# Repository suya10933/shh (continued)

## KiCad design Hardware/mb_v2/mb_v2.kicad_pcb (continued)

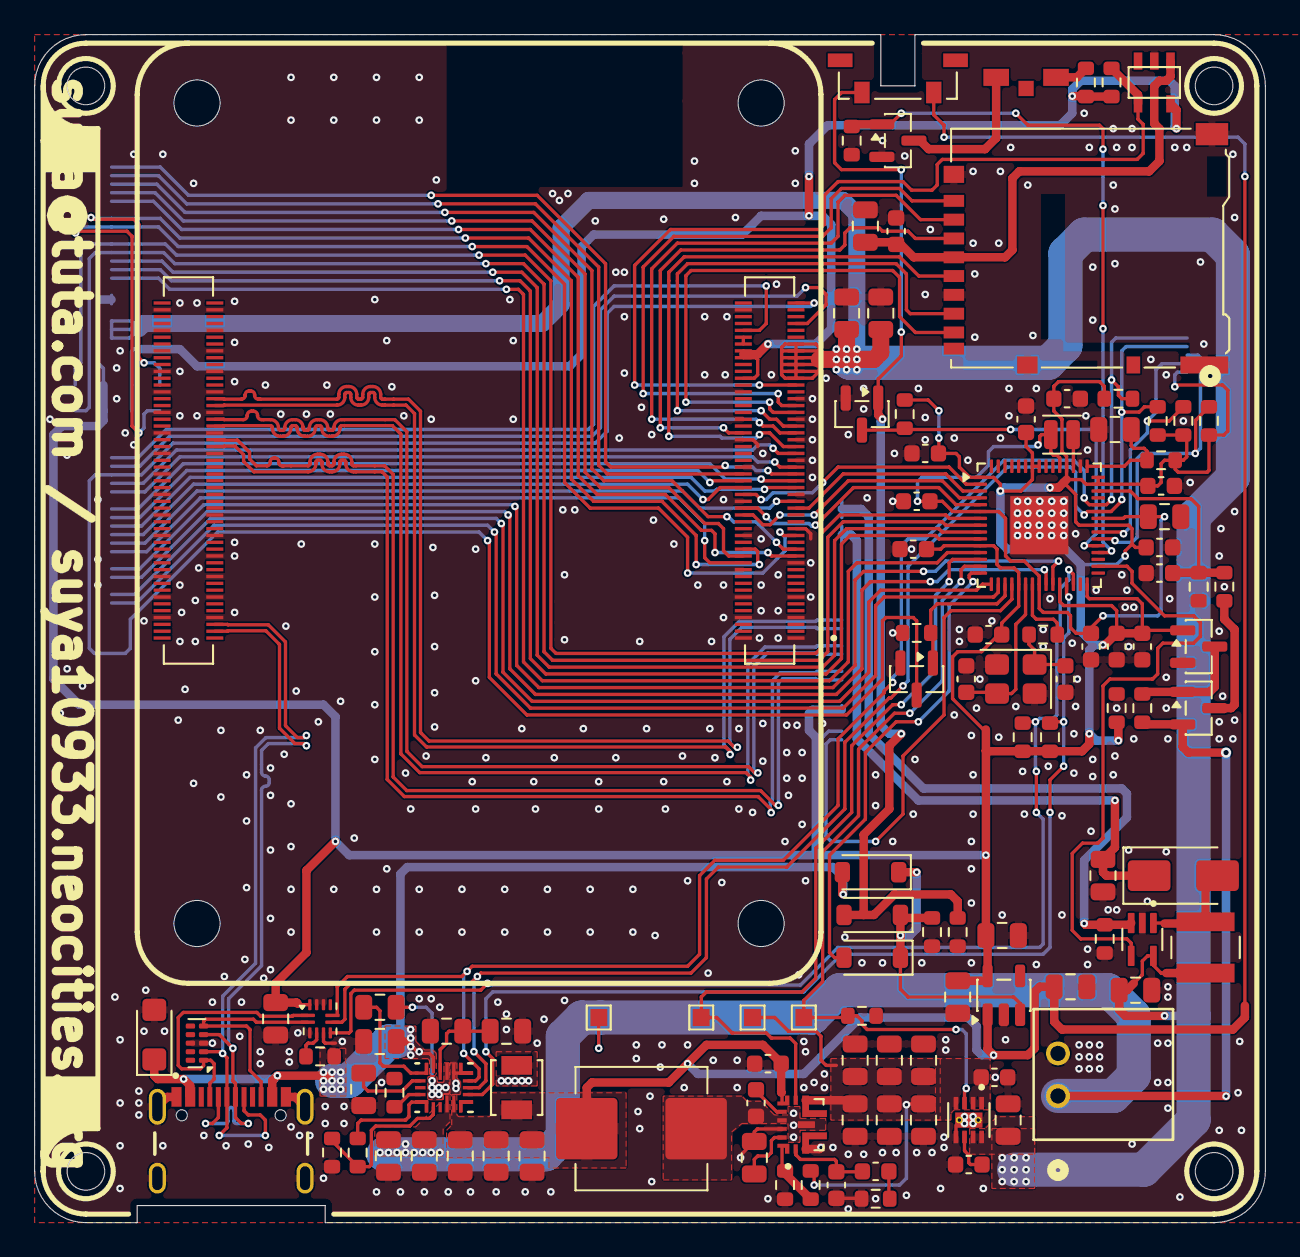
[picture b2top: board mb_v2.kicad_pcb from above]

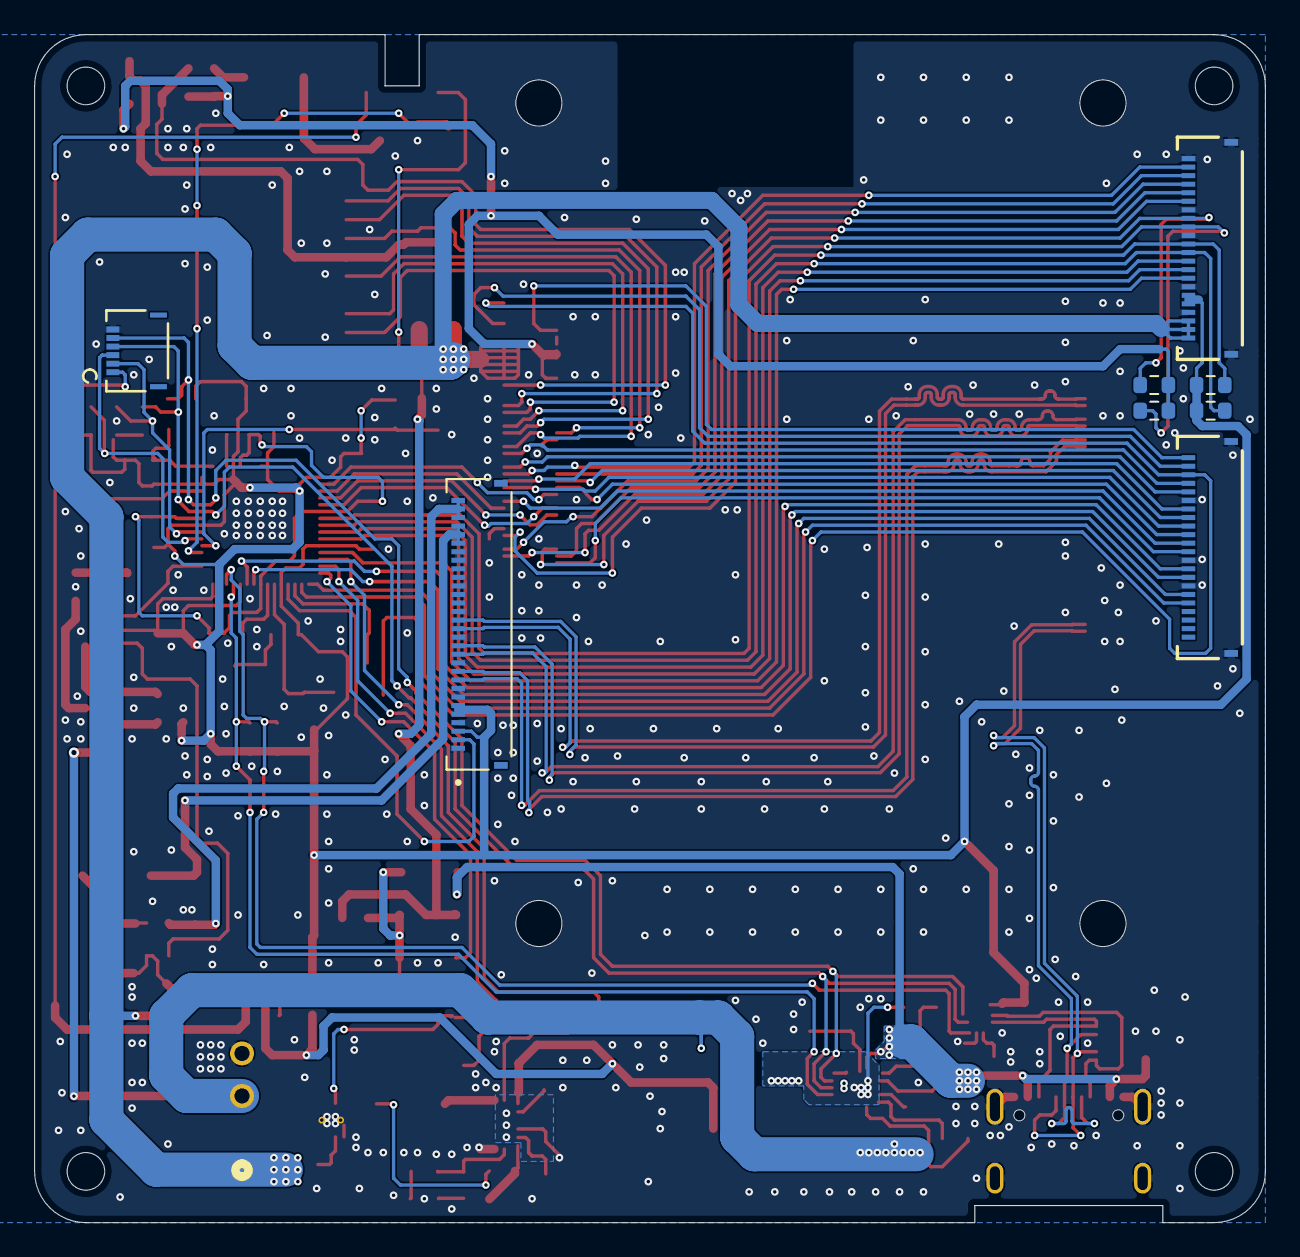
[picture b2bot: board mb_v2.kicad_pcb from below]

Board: 4 copper layers, 72.0 x 69.5 mm, 120 parts (8 on the bottom side), 103 nets.

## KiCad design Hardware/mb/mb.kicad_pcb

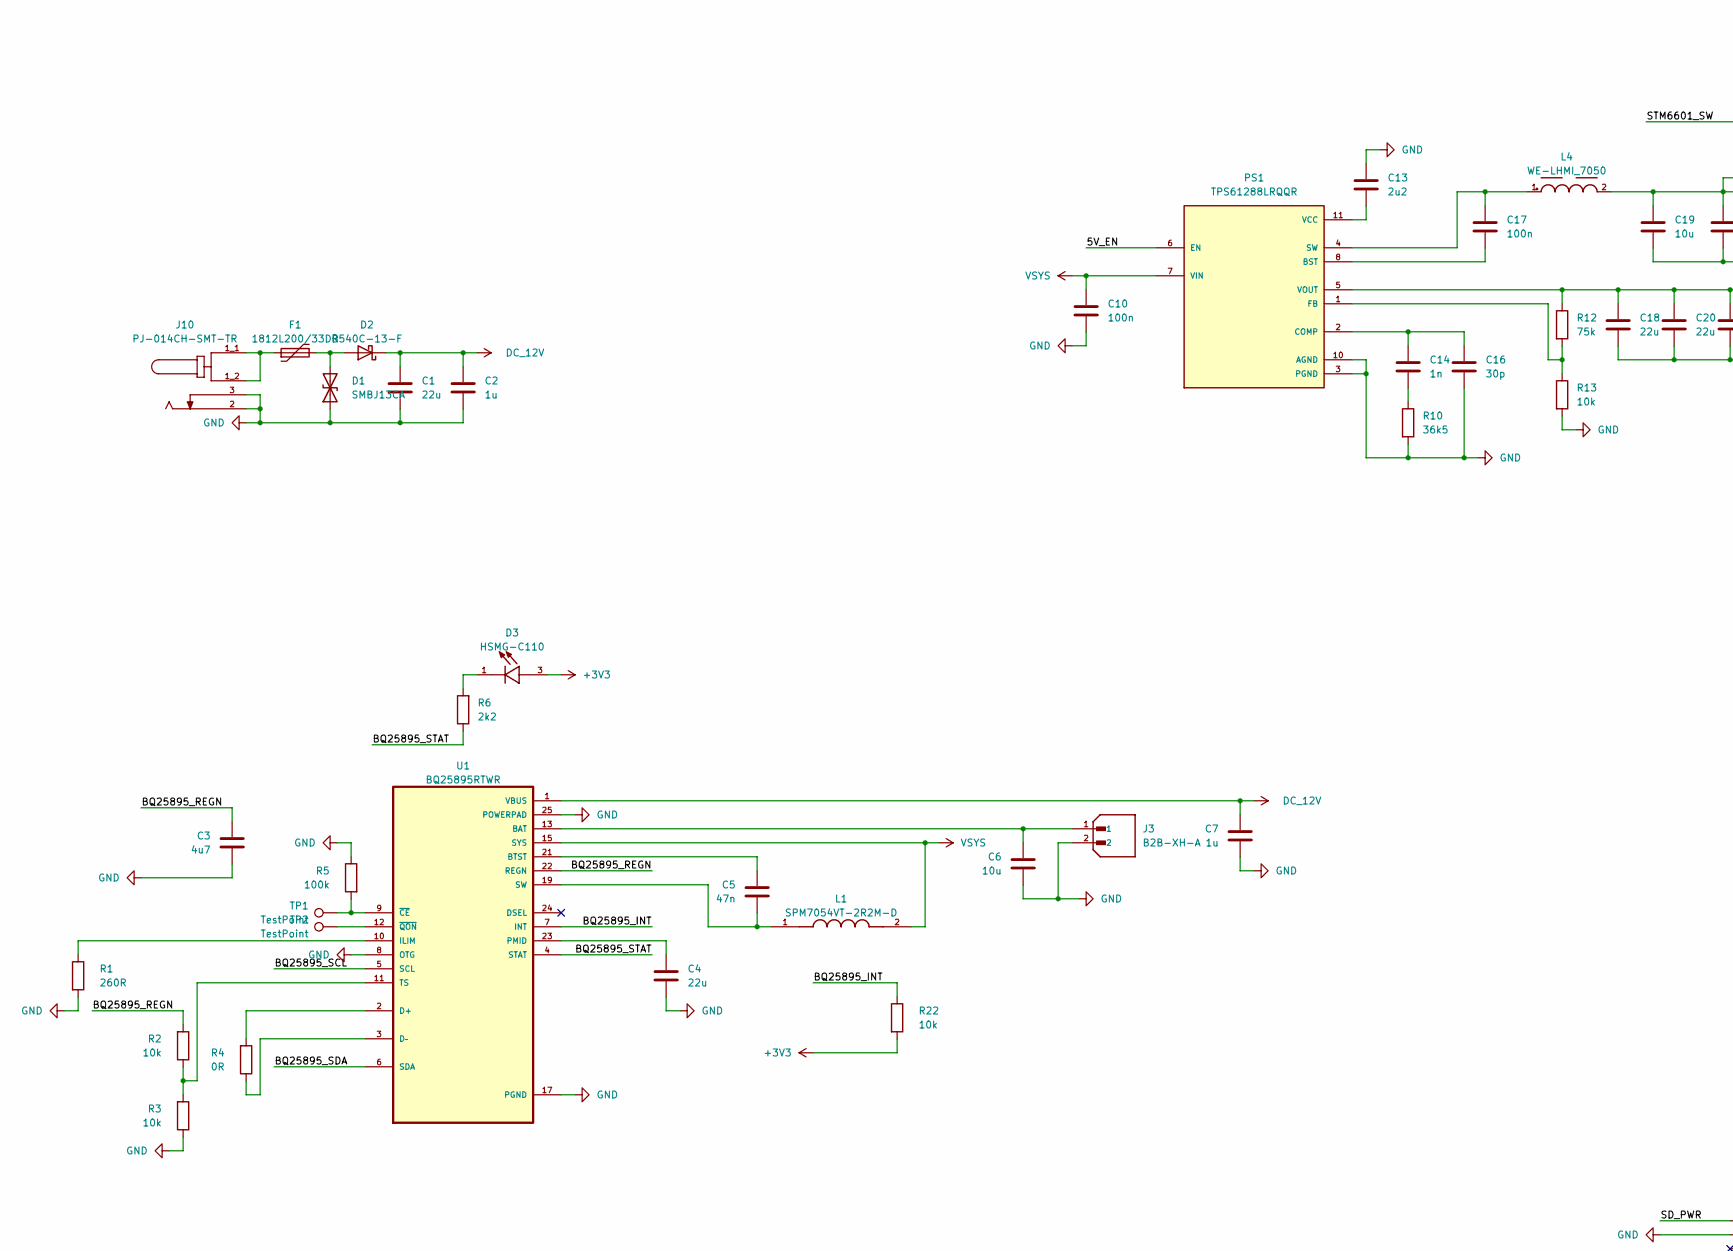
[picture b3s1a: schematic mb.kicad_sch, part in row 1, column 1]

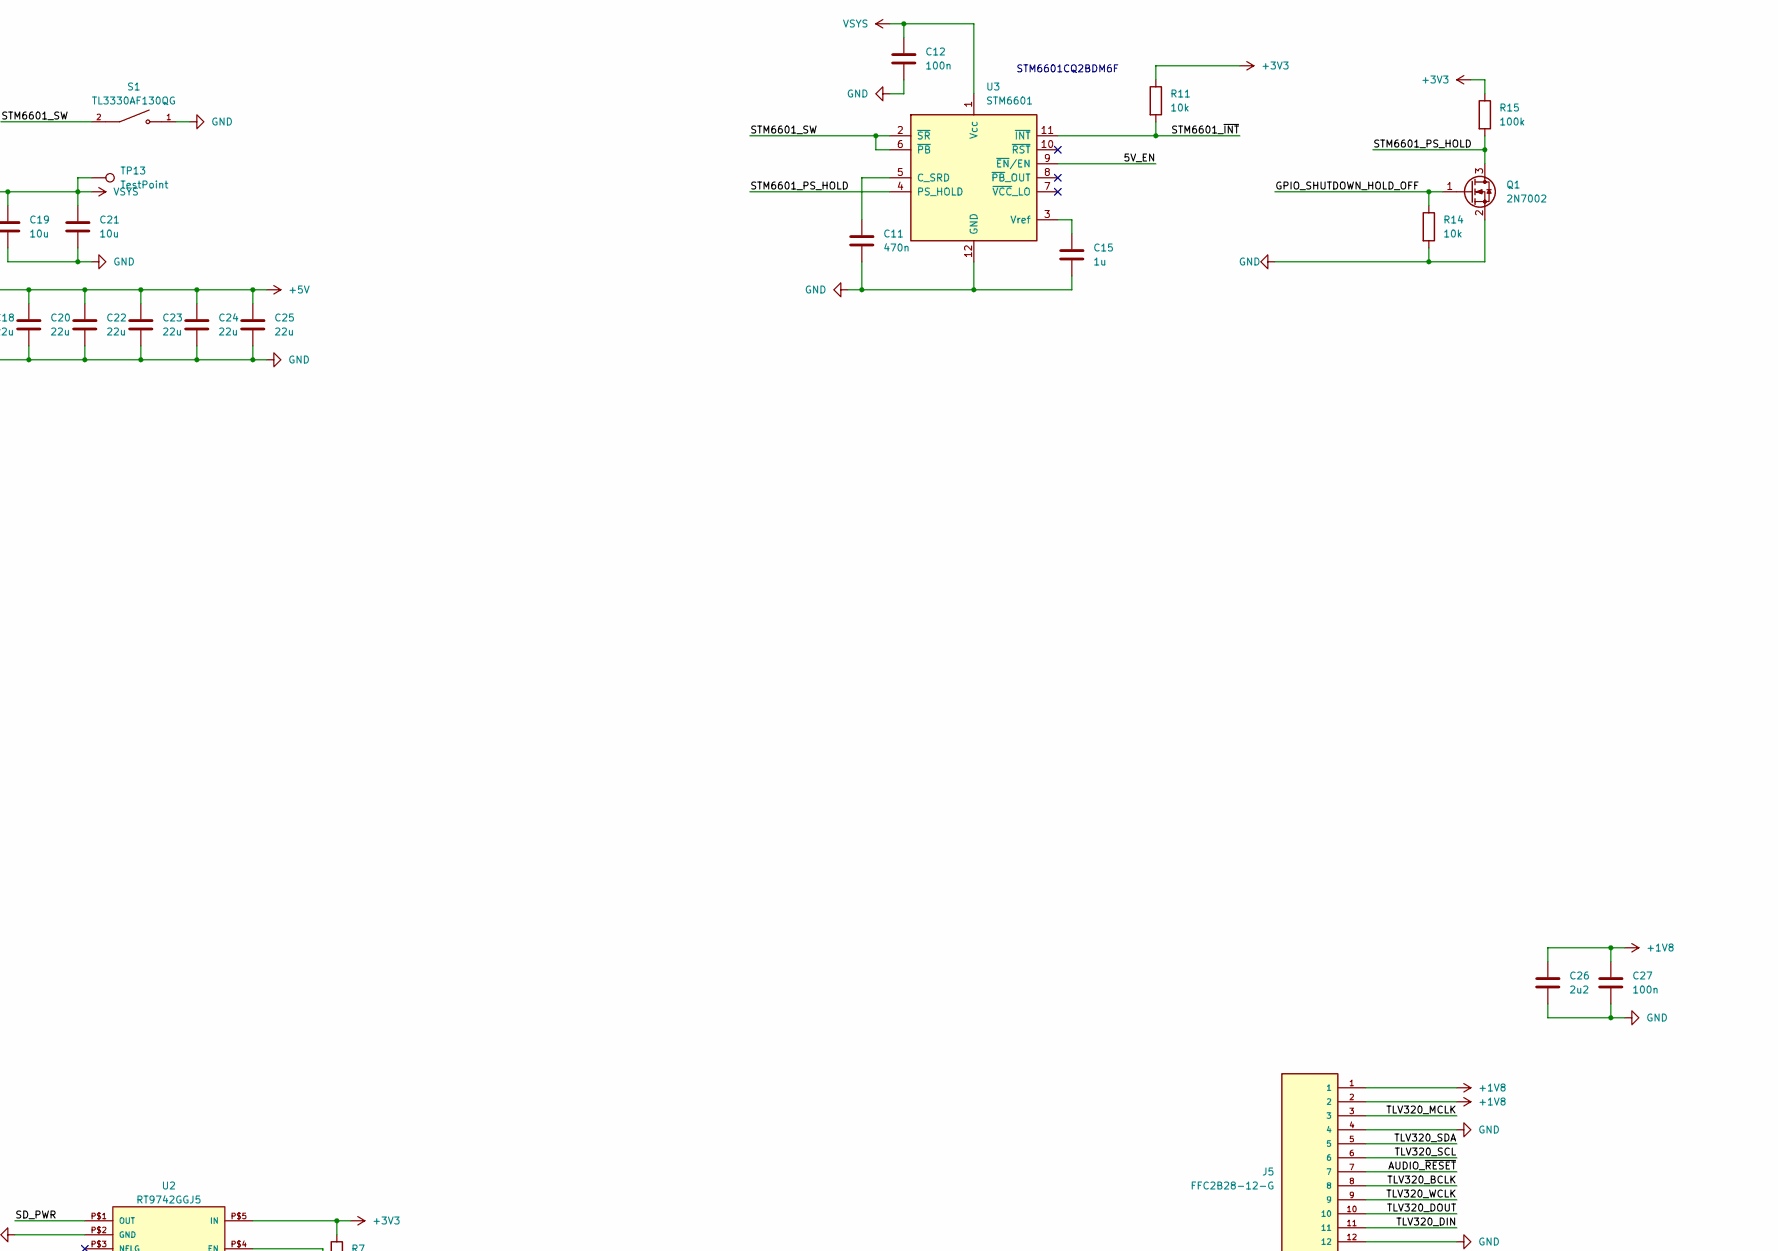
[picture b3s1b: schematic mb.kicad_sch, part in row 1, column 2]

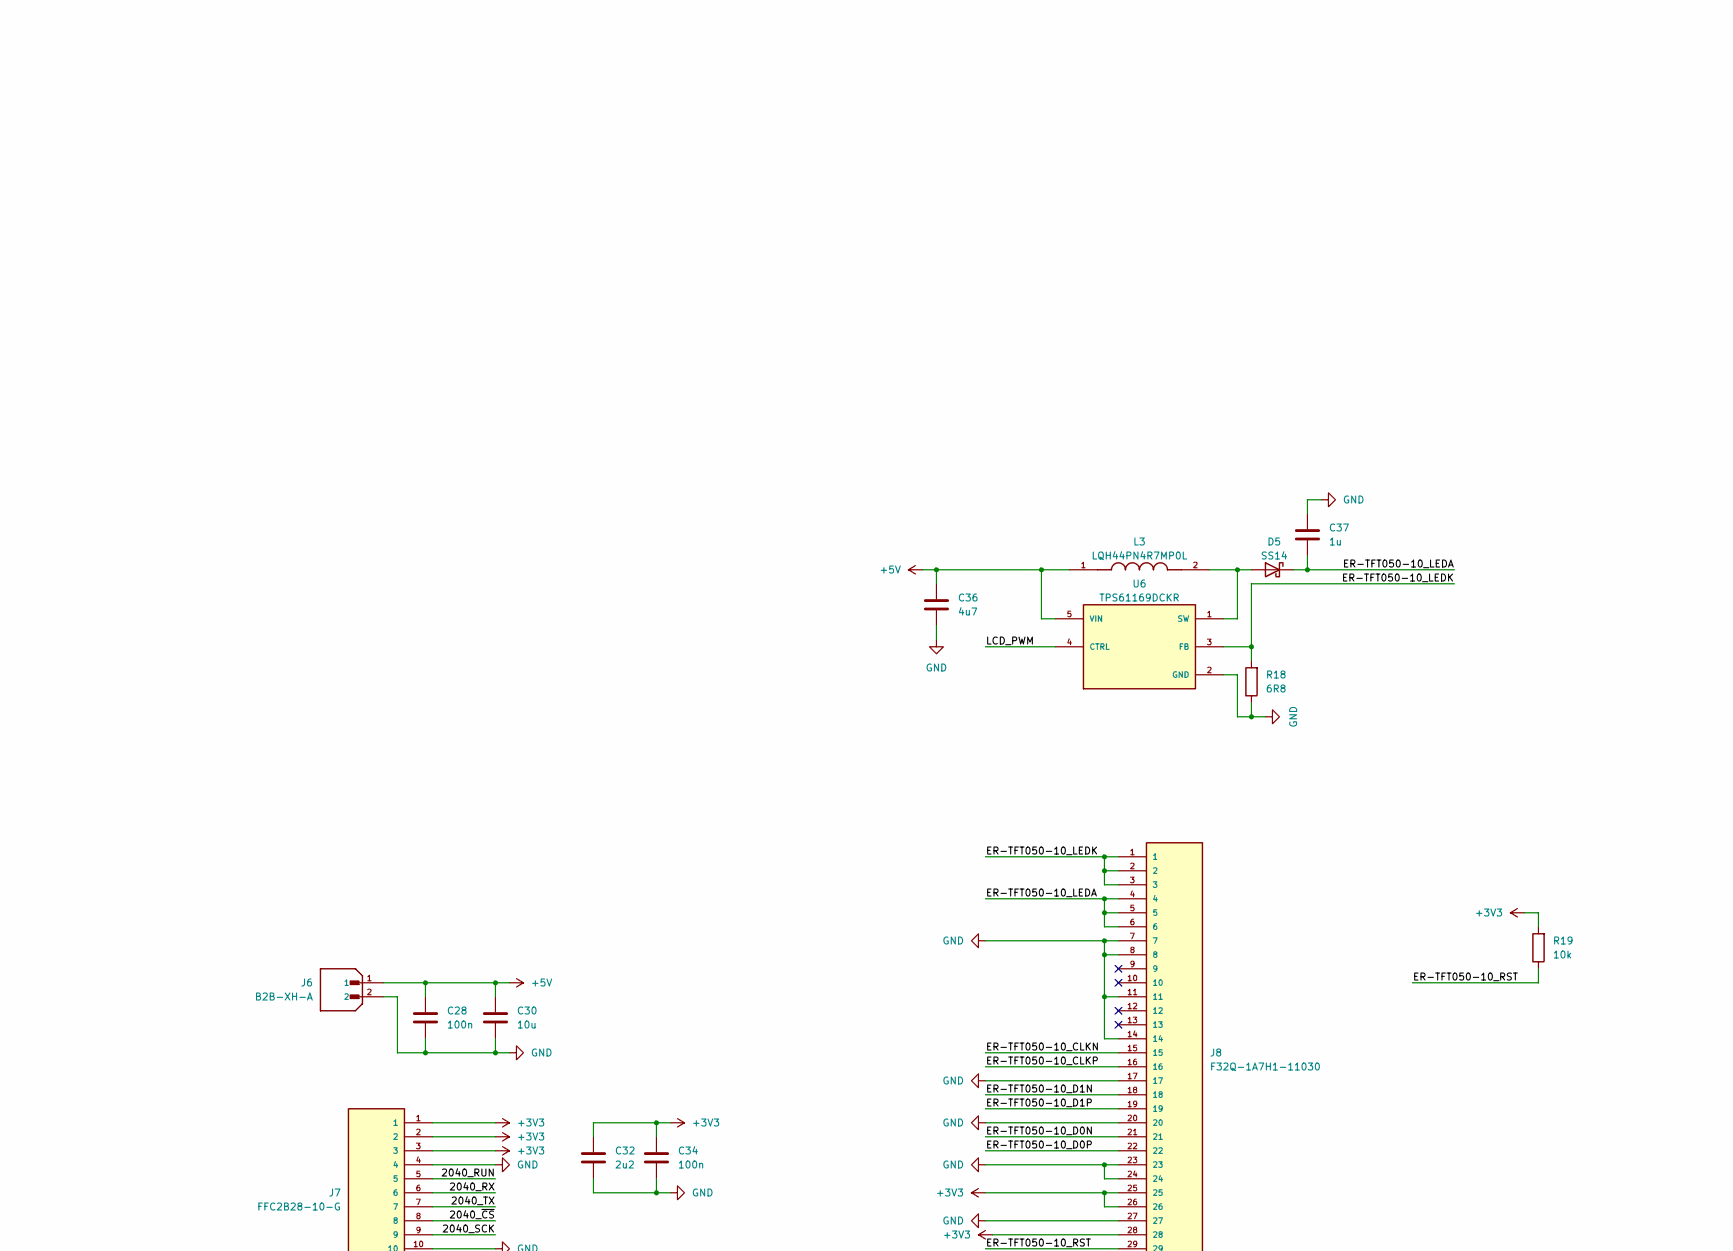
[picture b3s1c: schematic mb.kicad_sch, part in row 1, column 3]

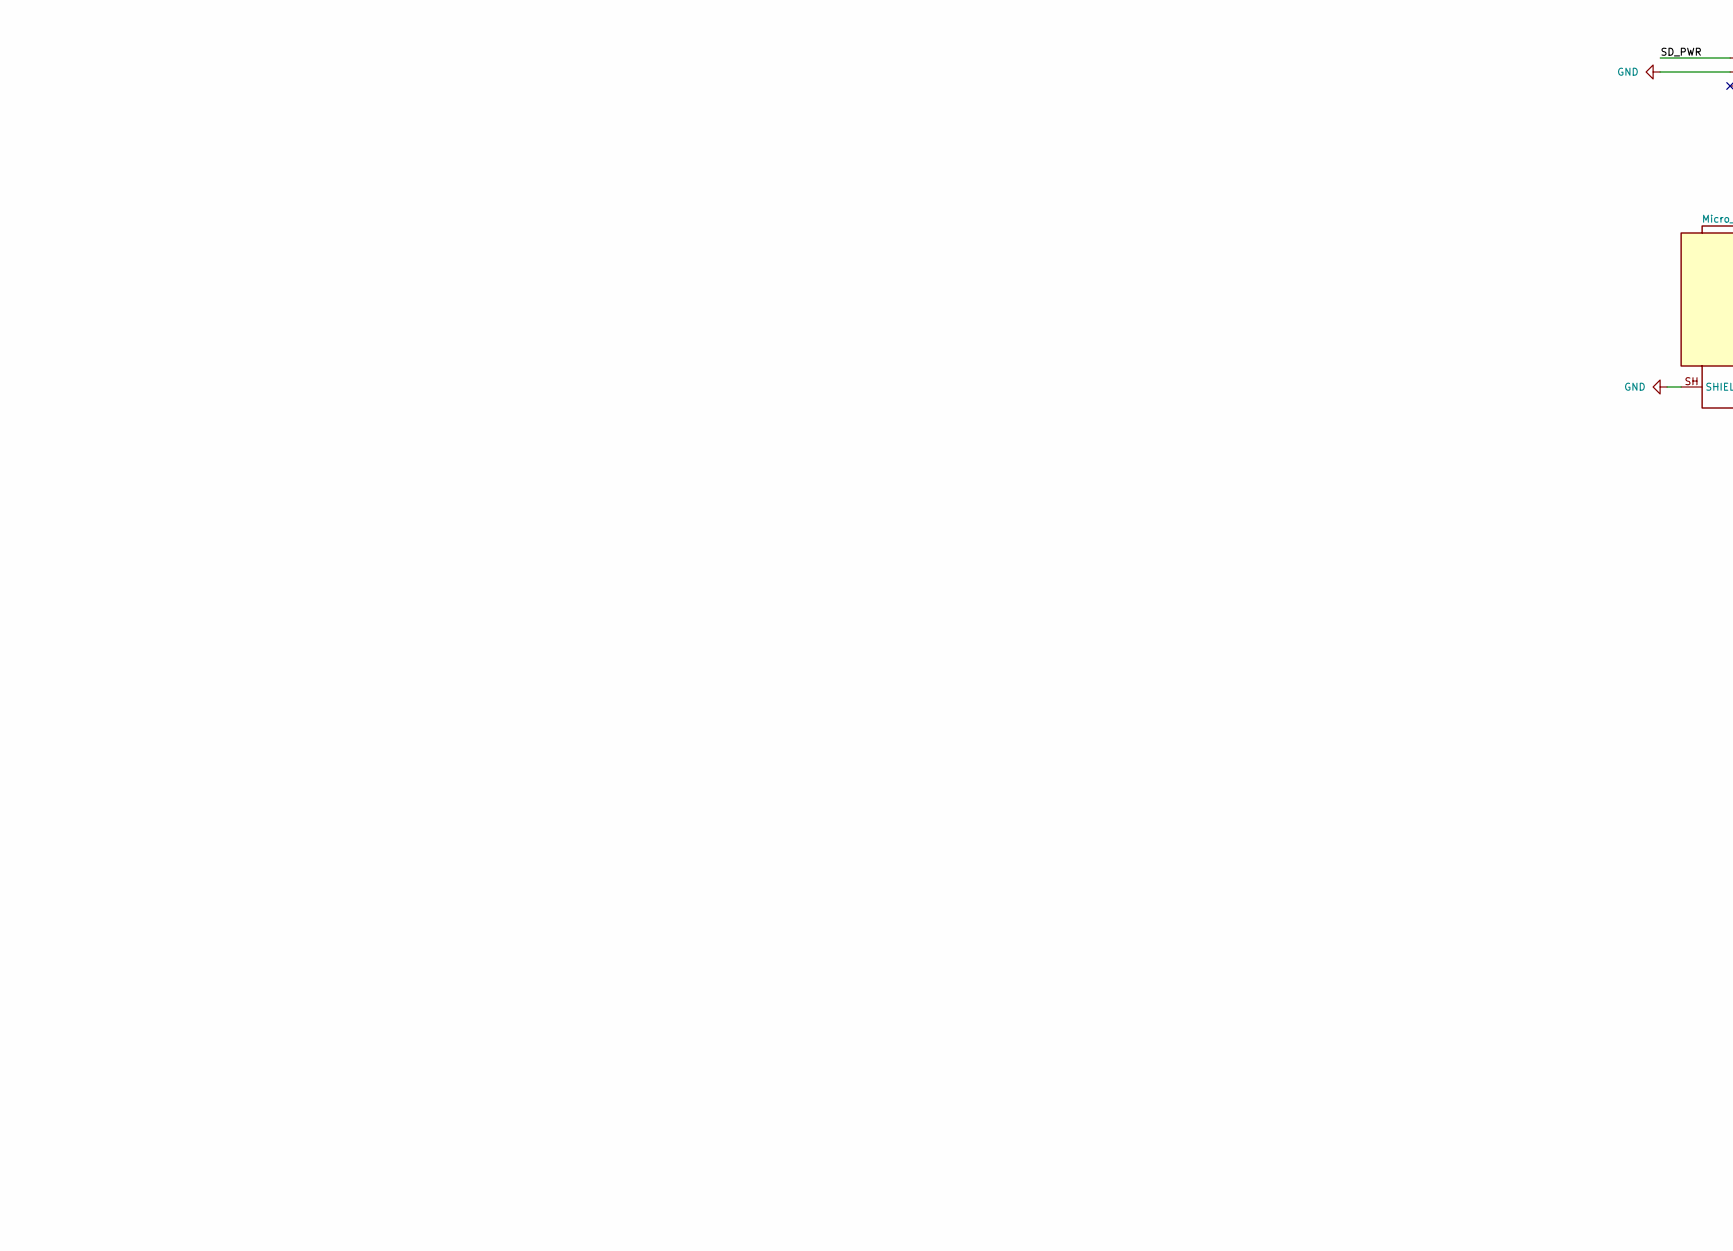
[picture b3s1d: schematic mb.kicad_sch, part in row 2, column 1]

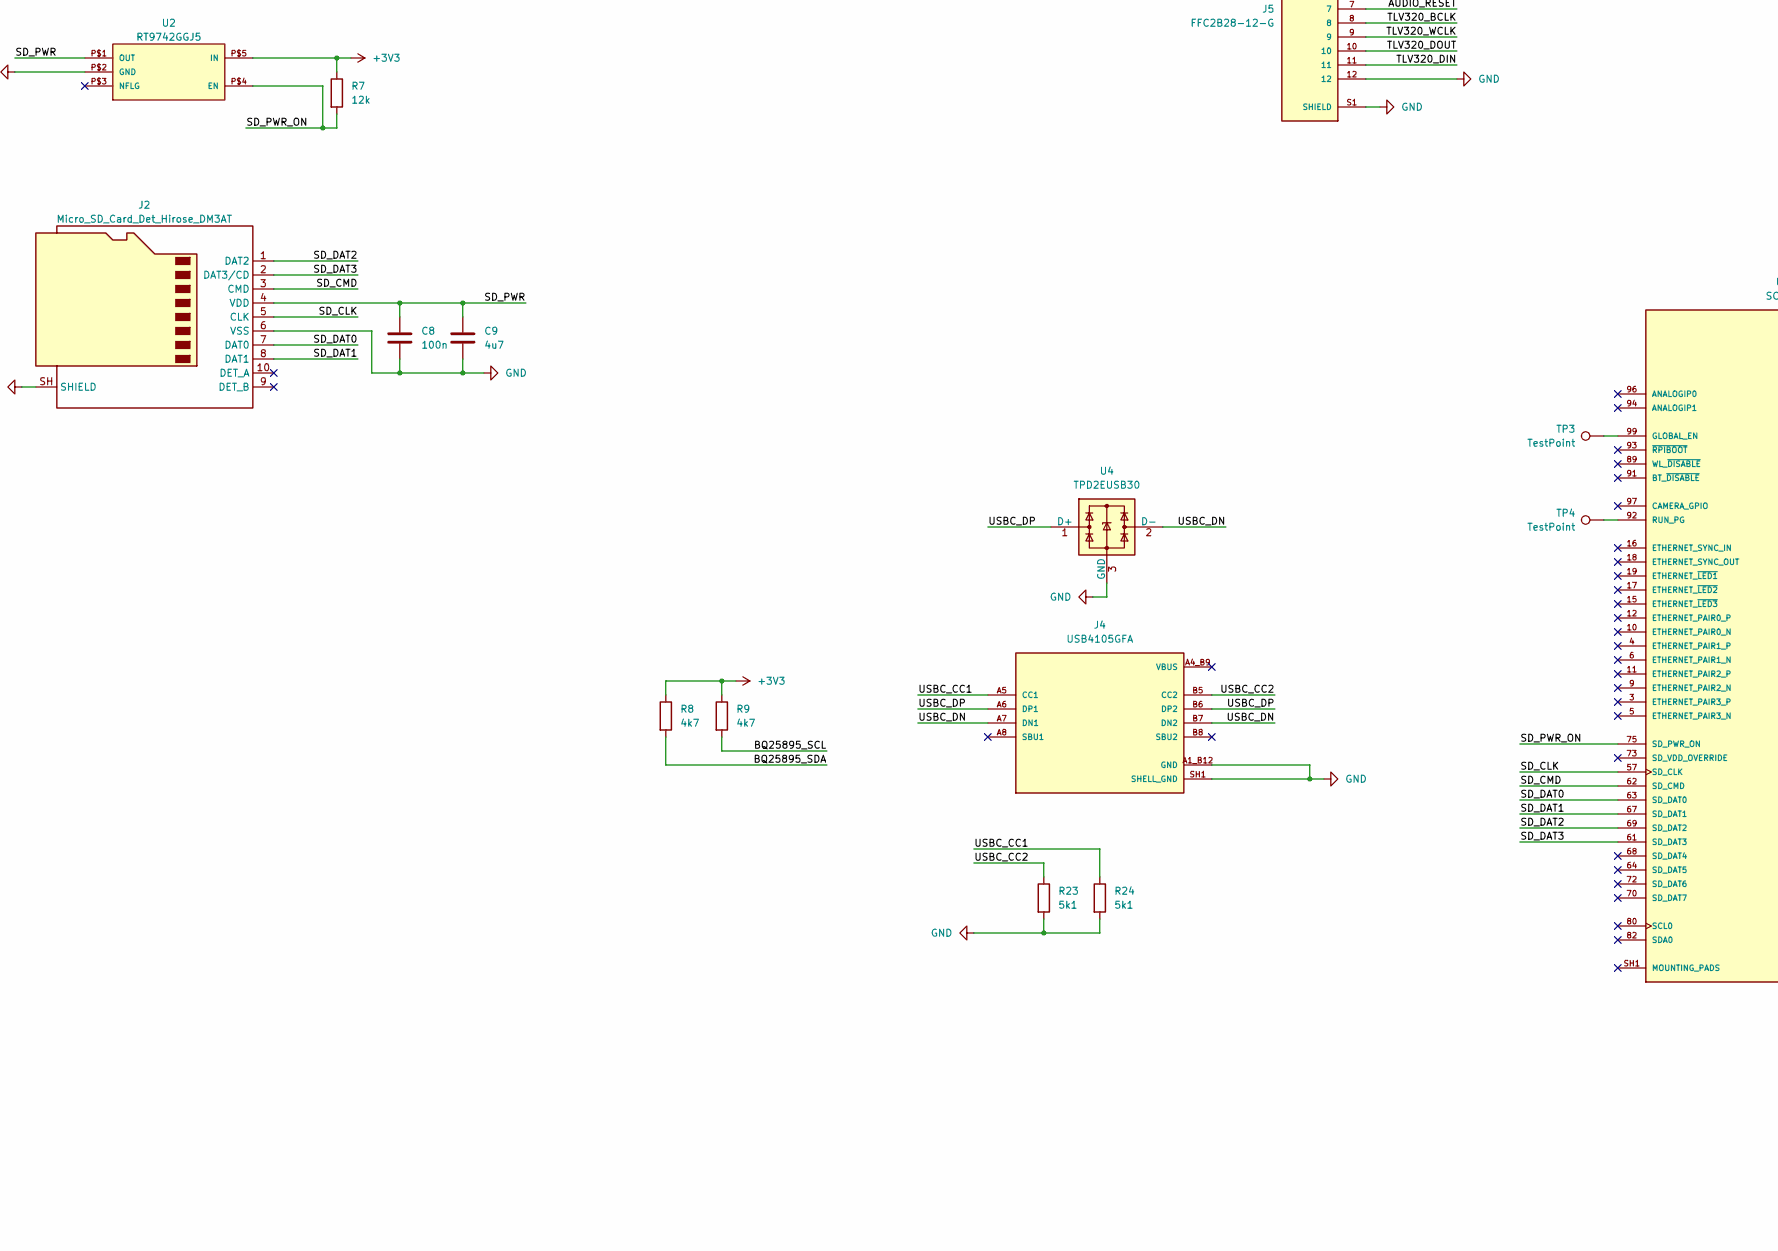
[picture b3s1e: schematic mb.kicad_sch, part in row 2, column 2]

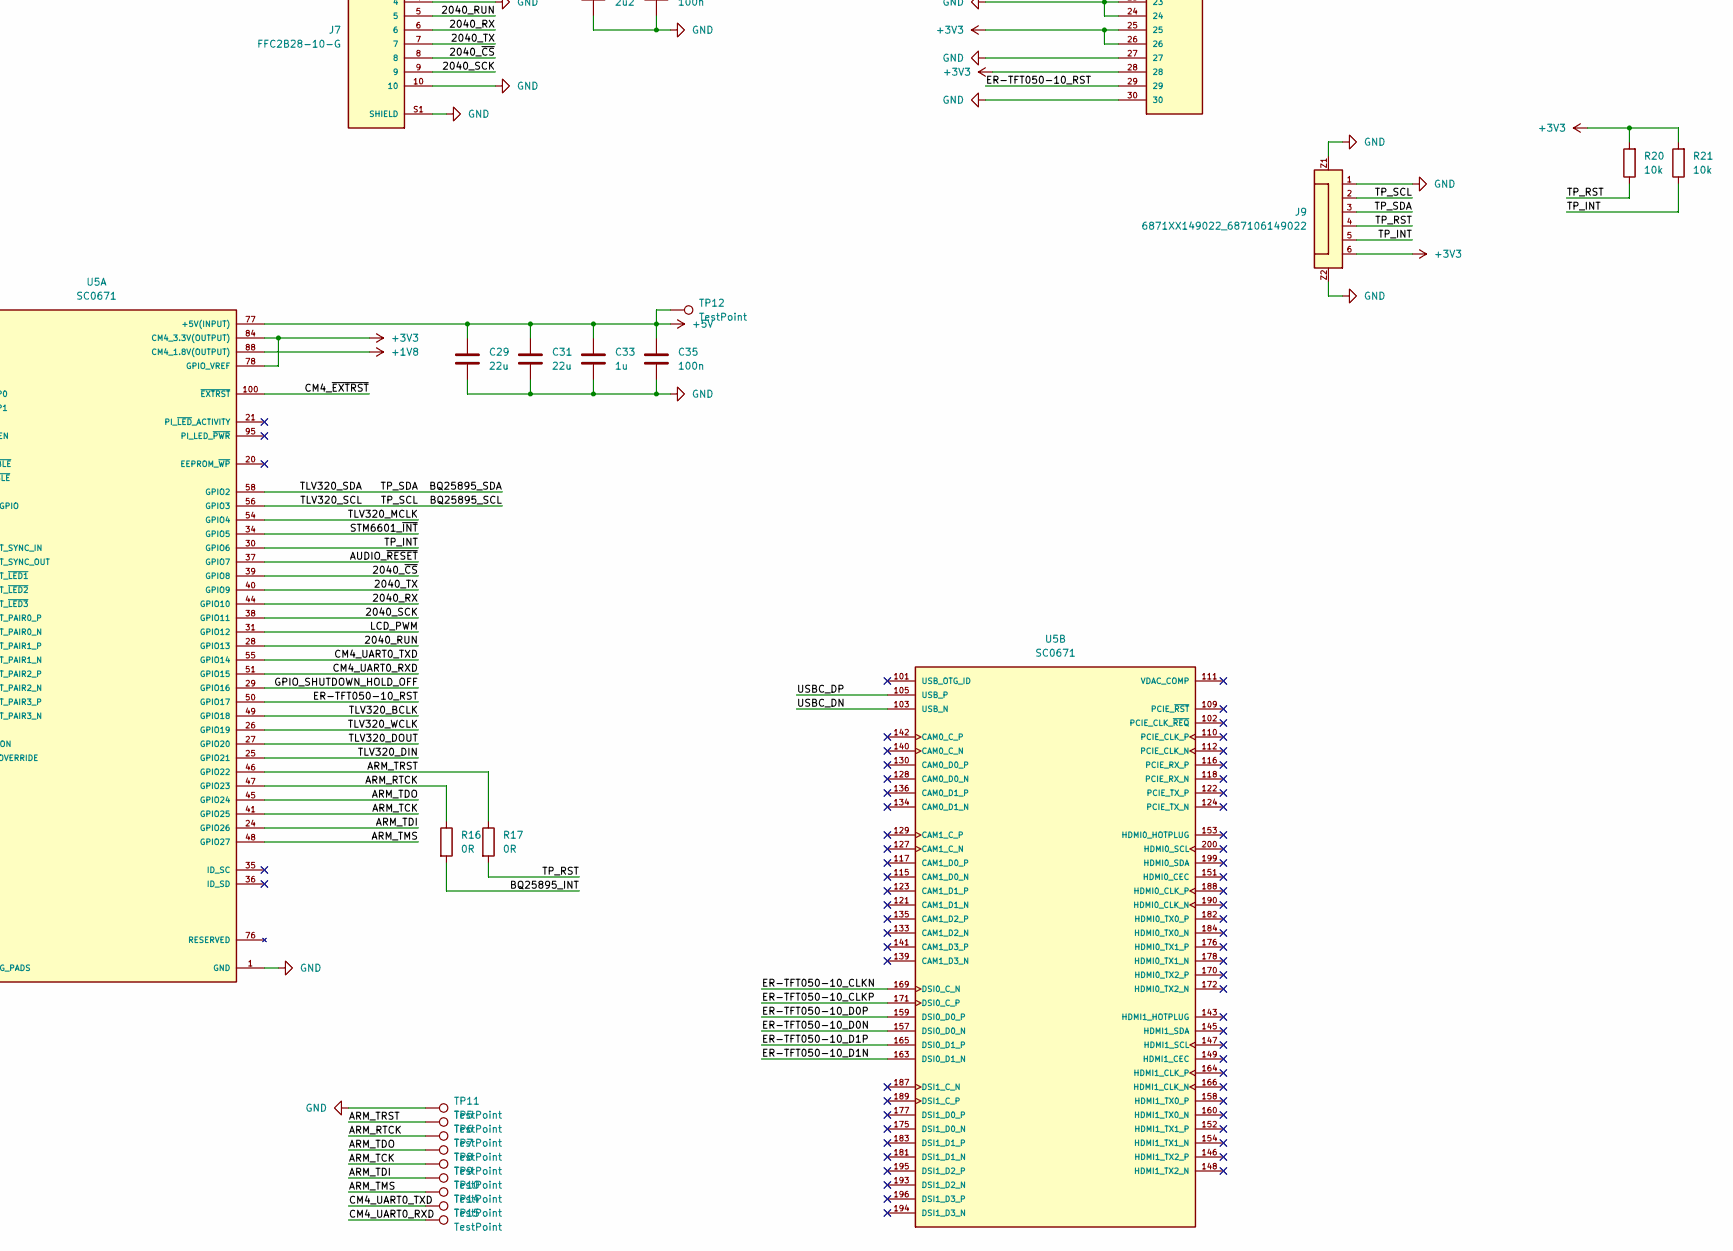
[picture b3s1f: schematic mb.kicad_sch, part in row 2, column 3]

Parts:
C1, C29, C31: 22u; C_1206_3216Metric
C2, C37: 1u; C_0805_2012Metric
C3, C9: 4u7; C_0805_2012Metric
C4, C18, C20, C22, C23, C24, C25: 22u; C_0805_2012Metric
C5: 47n; C_0603_1608Metric
C6, C19, C21, C30: 10u; C_0805_2012Metric
C7, C15, C33: 1u; C_0603_1608Metric
C8, C10, C12, C17, C27, C28, C34, C35: 100n; C_0603_1608Metric
C11: 470n; C_0603_1608Metric
C13, C26, C32: 2u2; C_0603_1608Metric
C14: 1n; C_0603_1608Metric
C16: 30p; C_0603_1608Metric
C36: 4u7; C_0603_1608Metric
D1: SMBJ13CA; D_SMB
D2: B540C-13-F; D_SMB
D3: HSMG-C110; LED_HSMG-C110; PARTREV March 25, 2022
D5: SS14; D_SMA
F1: 1812L200/33DR; Fuse_1812_4532Metric
J2: Micro_SD_Card_Det_Hirose_DM3AT; microSD_HC_Hirose_DM3AT-SF-PEJM5
J3, J6: B2B-XH-A; JST_B2B-XH-A; PARTREV N/A
J4: USB4105GFA; GCT_USB4105GFA; PARTREV B3
J5: FFC2B28-12-G; GCT_FFC2B28-12-G; PARTREV A
J7: FFC2B28-10-G; GCT_FFC2B28-10-G; PARTREV A
J8: F32Q-1A7H1-11030; AMPHENOL_F32Q-1A7H1-11030; PARTREV D
J9: 6871XX149022_687106149022; 687106149022
J10: PJ-014CH-SMT-TR; SAMESKY_PJ-014CH-SMT-TR; PARTREV 1.09
L1: SPM7054VT-2R2M-D; IND_SPM7054VT-2R2M-D; PARTREV 20200702
L3: LQH44PN4R7MP0L; IND_LQH44PN4R7MP0L; PARTREV N/A
L4: WE-LHMI_7050
PS1: TPS61288LRQQR; CONV_TPS61288LRQQR; PARTREV C
Q1: 2N7002; SOT-23
R1: 260R; R_0603_1608Metric
R2, R3, R11, R13, R14, R19, R20, R21, R22: 10k; R_0603_1608Metric
R4, R16, R17: 0R; R_0603_1608Metric
R5, R15: 100k; R_0603_1608Metric
R6: 2k2; R_0603_1608Metric
R7: 12k; R_0603_1608Metric
R8, R9: 4k7; R_0603_1608Metric
R10: 36k5; R_0603_1608Metric
R12: 75k; R_0603_1608Metric
R18: 6R8; R_0603_1608Metric
R23, R24: 5k1; R_0603_1608Metric
S1: TL3330AF130QG; SW_TL3330AF130QG; PARTREV B
TP1, TP2, TP3, TP4, TP5, TP6, TP7, TP8, TP9, TP10, TP11, TP12, TP13, TP14, TP15: TestPoint; TestPoint_Pad_D1.0mm
U1: BQ25895RTWR; QFN50P400X400X80-25N
U2: RT9742GGJ5; TSOT-23-5
U3: STM6601; TDFN-12_2x3mm_P0.5mm
U4: TPD2EUSB30; Texas_DRT-3
U5: SC0671; MODULE_SC0671; PARTREV 2021-10-12
U6: TPS61169DCKR; SOT65P210X110-5N; PARTREV A; DigiKey_Part_Number 296-40821-1-ND

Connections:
+1V8: C26.1, C27.1, J5.1, J5.2, U5.88 (CM4_1.8V(OUTPUT)), U5.90 (CM4_1.8V(OUTPUT))
+3V3: C32.1, C34.1, D3.3, J7.1, J7.2, J7.3, J8.25, J8.26, J8.28, J9.6, R7.1, R8.1, R9.1, R11.1, R15.1, R19.2, R20.2, R21.2, R22.2, U2.P$5 (IN), U5.78 (GPIO_VREF), U5.84 (CM4_3.3V(OUTPUT)), U5.86 (CM4_3.3V(OUTPUT))
+5V: C18.1, C20.1, C22.1, C23.1, C24.1, C25.1, C28.1, C29.1, C30.1, C31.1, C33.1, C35.1, C36.1, J6.1, L3.1, PS1.5 (VOUT), R12.1, TP12.1 (1_1), U5.77 (+5V(INPUT)), U5.79 (+5V(INPUT)), U5.81 (+5V(INPUT)), U5.83 (+5V(INPUT)), U5.85 (+5V(INPUT)), U5.87 (+5V(INPUT)), U6.5 (VIN)
/5V_EN: PS1.6 (EN), U3.9 (~EN/EN)
/2040_RUN: J7.5, U5.28 (GPIO13)
/2040_RX: J7.6, U5.44 (GPIO10)
/2040_SCK: J7.9, U5.38 (GPIO11)
/2040_TX: J7.7, U5.40 (GPIO9)
/2040_~CS: J7.8, U5.39 (GPIO8)
/ARM_RTCK: R16.1, TP6.1 (1_1), U5.47 (GPIO23)
/ARM_TCK: TP8.1 (1_1), U5.41 (GPIO25)
/ARM_TDI: TP9.1 (1_1), U5.24 (GPIO26)
/ARM_TDO: TP7.1 (1_1), U5.45 (GPIO24)
/ARM_TMS: TP10.1 (1_1), U5.48 (GPIO27)
/ARM_TRST: R17.1, TP5.1 (1_1), U5.46 (GPIO22)
/AUDIO_~RESET: J5.7, U5.37 (GPIO7)
/BQ25895_INT: R16.2, R22.1, U1.7 (INT)
/BQ25895_REGN: C3.1, R2.2, U1.22 (REGN)
/BQ25895_SCL: J5.6, J9.2, R9.2, U1.5 (SCL), U5.56 (GPIO3)
/BQ25895_SDA: J5.5, J9.3, R8.2, U1.6 (SDA), U5.58 (GPIO2)
/BQ25895_STAT: R6.1, U1.4 (STAT)
/CM4_UART0_RXD: TP15.1 (1_1), U5.51 (GPIO15)
/CM4_UART0_TXD: TP14.1 (1_1), U5.55 (GPIO14)
/CM4_~EXTRST: U5.100 (~EXTRST)
/ER-TFT050-10_CLKN: J8.15, U5.169 (DSI0_C_N)
/ER-TFT050-10_CLKP: J8.16, U5.171 (DSI0_C_P)
/ER-TFT050-10_D0N: J8.21, U5.157 (DSI0_D0_N)
/ER-TFT050-10_D0P: J8.22, U5.159 (DSI0_D0_P)
/ER-TFT050-10_D1N: J8.18, U5.163 (DSI0_D1_N)
/ER-TFT050-10_D1P: J8.19, U5.165 (DSI0_D1_P)
/ER-TFT050-10_LEDA: C37.2, D5.1 (K), J8.4, J8.5, J8.6
/ER-TFT050-10_LEDK: J8.1, J8.2, J8.3, R18.2, U6.3 (FB)
/ER-TFT050-10_RST: J8.29, R19.1, U5.50 (GPIO17)
/GPIO_SHUTDOWN_HOLD_OFF: Q1.1 (G), R14.1, U5.29 (GPIO16)
/LCD_PWM: U5.31 (GPIO12), U6.4 (CTRL)
/SD_CLK: J2.5 (CLK), U5.57 (SD_CLK)
/SD_CMD: J2.3 (CMD), U5.62 (SD_CMD)
/SD_DAT0: J2.7 (DAT0), U5.63 (SD_DAT0)
/SD_DAT1: J2.8 (DAT1), U5.67 (SD_DAT1)
/SD_DAT2: J2.1 (DAT2), U5.69 (SD_DAT2)
/SD_DAT3: J2.2 (DAT3/CD), U5.61 (SD_DAT3)
/SD_PWR: C8.1, C9.1, J2.4 (VDD), U2.P$1 (OUT)
/SD_PWR_ON: R7.2, U2.P$4 (EN), U5.75 (SD_PWR_ON)
/STM6601_PS_HOLD: Q1.3 (D), R15.2, U3.4 (PS_HOLD)
/STM6601_SW: S1.2, U3.2 (~SR), U3.6 (~PB)
/STM6601_~INT: R11.2, U3.11 (~INT), U5.34 (GPIO5)
/TLV320_BCLK: J5.8, U5.49 (GPIO18)
/TLV320_DIN: J5.11, U5.25 (GPIO21)
/TLV320_DOUT: J5.10, U5.27 (GPIO20)
/TLV320_MCLK: J5.3, U5.54 (GPIO4)
/TLV320_WCLK: J5.9, U5.26 (GPIO19)
/TP_INT: J9.5, R21.1, U5.30 (GPIO6)
/TP_RST: J9.4, R17.2, R20.1
/USBC_CC1: J4.A5 (CC1), R24.1
/USBC_CC2: J4.B5 (CC2), R23.1
/USBC_DN: J4.A7 (DN1), J4.B7 (DN2), U4.2 (D-), U5.103 (USB_N)
/USBC_DP: J4.A6 (DP1), J4.B6 (DP2), U4.1 (D+), U5.105 (USB_P)
BAT: C6.1, J3.1, U1.13 (BAT), U1.14 (BAT)
DC_12V: C1.1, C2.1, C7.1, D2.1 (K), U1.1 (VBUS)
GND: C1.2, C2.2, C3.2, C4.2, C6.2, C7.2, C8.2, C9.2, C10.2, C11.2, C12.2, C13.1, C15.2, C16.2, C18.2, C19.2, C20.2, C21.2, C22.2, C23.2, C24.2, C25.2, C26.2, C27.2, C28.2, C29.2, C30.2, C31.2, C32.2, C33.2, C34.2, C35.2, C36.2, C37.1, D1.1 (A1), J2.6 (VSS), J2.SH (SHIELD), J3.2, J4.A1_B12 (GND), J4.B1_A12 (GND), J4.SH1 (SHELL_GND), J4.SH2 (SHELL_GND), J4.SH3 (SHELL_GND), J4.SH4 (SHELL_GND), J5.4, J5.12, J5.S1 (SHIELD), J5.S2 (SHIELD), J6.2, J7.4, J7.10, J7.S1 (SHIELD), J7.S2 (SHIELD), J8.7, J8.8, J8.11, J8.14, J8.17, J8.20, J8.23, J8.24, J8.27, J8.30, J9.1, J9.Z1, J9.Z2, J10.2, J10.3, PS1.3 (PGND), PS1.10 (AGND), Q1.2 (S), R1.2, R3.1, R5.1, R10.2, R13.2, R14.2, R18.1, R23.2, R24.2, S1.1, TP11.1 (1_1), U1.8 (OTG), U1.17 (PGND), U1.18 (PGND), U1.25 (POWERPAD), U2.P$2 (GND), U3.12 (GND), U4.3 (GND), U5.1 (GND), U5.2 (GND), U5.7 (GND), U5.8 (GND), U5.13 (GND), U5.14 (GND), U5.22 (GND), U5.23 (GND), U5.32 (GND), U5.33 (GND), U5.42 (GND), U5.43 (GND), U5.52 (GND), U5.53 (GND), U5.59 (GND), U5.60 (GND), U5.65 (GND), U5.66 (GND), U5.71 (GND), U5.74 (GND), U5.98 (GND), U5.107 (GND), U5.108 (GND), U5.113 (GND), U5.114 (GND), U5.119 (GND), U5.120 (GND), U5.125 (GND), U5.126 (GND), U5.131 (GND), U5.132 (GND), U5.137 (GND), U5.138 (GND), U5.144 (GND), U5.150 (GND), U5.155 (GND), U5.156 (GND), U5.161 (GND), U5.162 (GND), U5.167 (GND), U5.168 (GND), U5.173 (GND), U5.174 (GND), U5.179 (GND), U5.180 (GND), U5.185 (GND), U5.186 (GND), U5.191 (GND), U5.192 (GND), U5.197 (GND), U5.198 (GND), U6.2 (GND)
unnamed: C14.2, R10.1
unnamed: C17.1, L4.1, PS1.4 (SW), PS1.9 (SW)
unnamed: D1.2 (A2), D2.2 (A), F1.2
unnamed: D3.1, R6.2
unnamed: D5.2 (A), L3.2, U6.1 (SW)
unnamed: F1.1, J10.1_1, J10.1_2
unnamed: C17.2, PS1.8 (BST)
unnamed: C14.1, C16.1, PS1.2 (COMP)
unnamed: PS1.1 (FB), R12.2, R13.1
unnamed: C13.2, PS1.11 (VCC)
unnamed: C5.1, U1.21 (BTST)
unnamed: R4.2, U1.2 (D+)
unnamed: R4.1, U1.3 (D–)
unnamed: R1.1, U1.10 (ILIM)
unnamed: C4.1, U1.23 (PMID)
unnamed: R2.1, R3.2, U1.11 (TS)
unnamed: R5.2, TP1.1 (1_1), U1.9 (~CE)
unnamed: TP2.1 (1_1), U1.12 (~QON)
unnamed: C11.1, U3.5 (C_SRD)
unnamed: C15.1, U3.3 (Vref)
unnamed: TP3.1 (1_1), U5.99 (GLOBAL_EN)
unnamed: TP4.1 (1_1), U5.92 (RUN_PG)
SW: C5.2, L1.1, U1.19 (SW), U1.20 (SW)
VSYS: C10.1, C12.1, C19.1, C21.1, L1.2, L4.2, PS1.7 (VIN), TP13.1 (1_1), U1.15 (SYS), U1.16 (SYS), U3.1 (Vcc)

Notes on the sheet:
STM6601CQ2BDM6F

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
